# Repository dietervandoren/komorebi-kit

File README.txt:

//~~~~~~~~~~~~~~~~~~~~~~~~~~~~~~~~~~~~~~~~~~~~~~~~~~~~~~~~~~~~~~~~~~~~~~~~~~~~~
//
// KOMOREBI KIT, 2021 
//
// Created by Matteo Marangoni & Dieter Vandoren 
// Programming by Riccardo Marogna
// PCB design by Daan Johan 
//
// Info & documentation: https://instrumentinventors.org/editions/iii-sensory-kit-komorebi-instructions/ 
// GitHub: https://github.com/dietervandoren/komorebi-kit 
//
// KOMOREBI KIT is licensed under a Creative Commons Attribution-NonCommercial-ShareAlike 4.0 International License, 
// which is detailed in License.txt 
//
// KOMOREBI KIT includes the Mozzi sound synthesis library under a Creative Commons Attribution-NonCommercial-ShareAlike 4.0 International License.
// Mozzi is created by Tim Barrass, webpage: https://sensorium.github.com/Mozzi/ 
// 
//~~~~~~~~~~~~~~~~~~~~~~~~~~~~~~~~~~~~~~~~~~~~~~~~~~~~~~~~~~~~~~~~~~~~~~~~~~~~~

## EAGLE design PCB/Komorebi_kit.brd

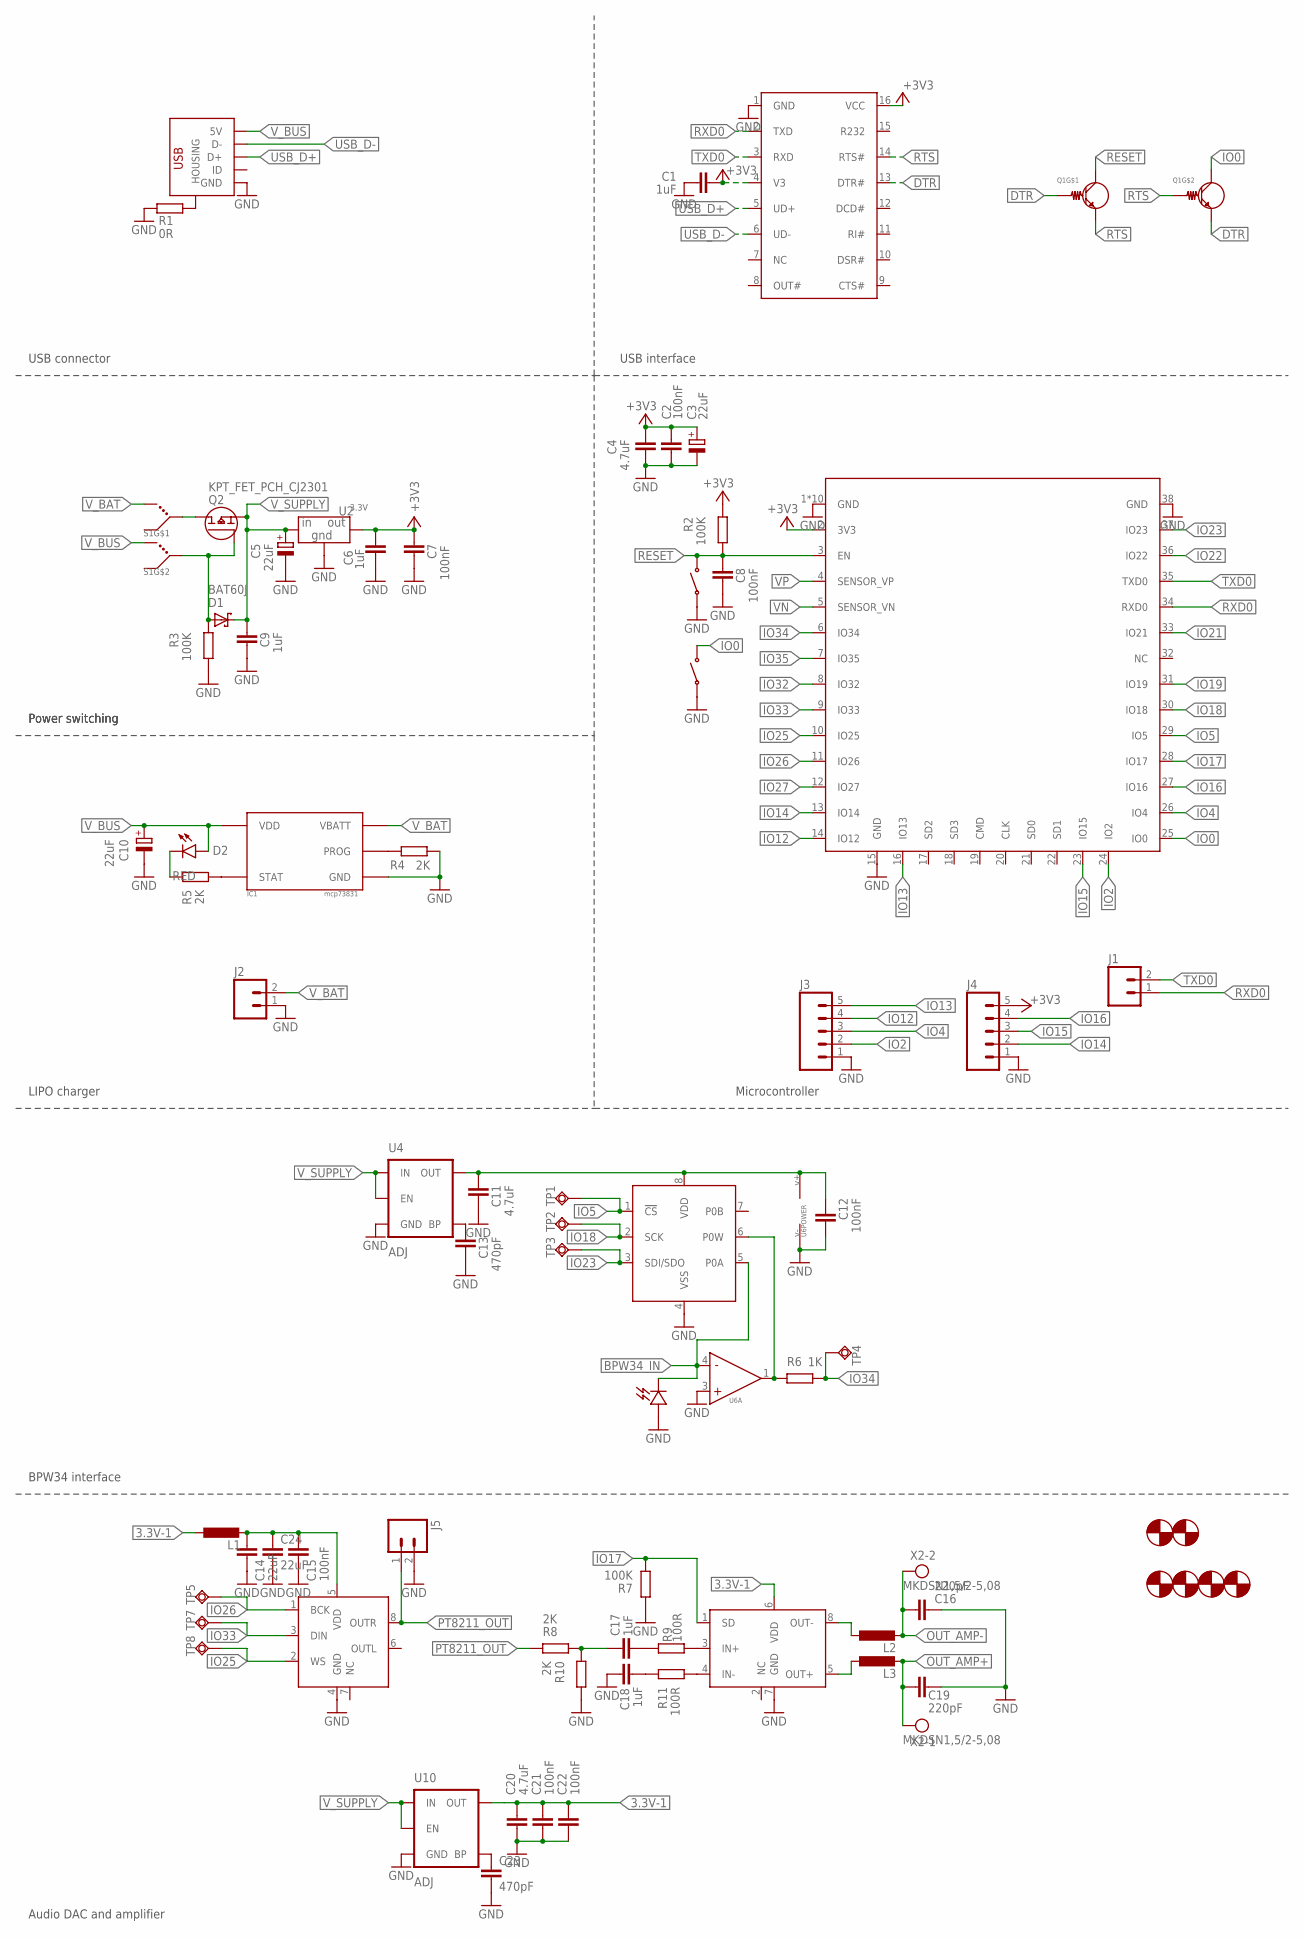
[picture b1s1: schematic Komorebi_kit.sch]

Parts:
C1, C6, C9, C17, C18: 1uF; C0603
C2, C7, C8, C12, C15, C21, C22: 100nF; C0603
C3, C5, C10: 22uF; PANASONIC_B
C4, C11, C20: 4.7uF; C0603
C13, C23: 470pF; C0603
C14, C24: 22uF; C0805
C16, C19: 220pF; C0603
D1: BAT60J; SOD323_ST
D2: RED; LED-1206
D3: KPT_SENSORS_BPW34; BPW34
H1, H2: KPT_HOLE3.0; 3.0MOUNTHOLE
H3, H4, H5, H6: KPT_HOLE4.1; 4.1MOUNTHOLE
IC1: KPT_CHARGER_MCP73831; SOT23-5
J1, J2, J5: M02PTH; 1X02
J3, J4: M05PTH; 1X05
L1, L2, L3: L-EUL2012C; L2012C
Q1: KPT_UMH3N; SOT363
Q2: KPT_FET_PCH_CJ2301; SOT23
R1: 0R; R0603
R2, R3, R7: 100K; R0603
R4, R5, R8, R10: 2K; R0603
R6: 1K; R0603
R9, R11: 100R; R0603
S1: KPT_SWITCH_JS202011AQN; C&K_JS202011AQN
S2, S3: TACT_SWITCH_C318884; SWITCH_TACTILE_C318884
TP1, TP2, TP3, TP4, TP5, TP7, TP8: TPSQB1,27; B1,27
U1: KPT_CH340C; SOIC16
U2: 3.3V; SOT-89-3L
U3: KPT_ESP32; WROOM_ESP32
U4, U10: ADJ; SOT23-5
U5: KPT_DIGIPOT_MCP41X1SOIC8; SOIC-8
U6: KPT_OPAMP_MCP6001; SOT23-5
U7: KPT_DAC_PT8211; SOIC-8
U8: KPT_AMP-D_PAM8302SOIC8; SOIC-8
X1: USB_MICROB_C10418
X2: MKDSN1,5/2-5,08

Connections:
3.3V-1: C20.1, C21.1, C22.1, L1.1, U8.6 (VDD), U10.5 (OUT)
+3V3: C1.2, C2.1, C3.+, C4.2, C6.1, C7.1, J4.5, R2.2, U1.4 (V3), U1.16 (VCC), U2.P$3 (OUT), U3.2 (3V3)
BPW34_IN: D3.CATHODE, U5.5 (P0A), U6.4 (-)
DTR: Q1.2 (BASE), Q1.4 (EMITTER), U1.13 (DTR#)
GND: C1.1, C2.2, C3.-, C4.1, C5.-, C6.2, C7.2, C8.2, C9.2, C10.-, C11.2, C12.2, C13.2, C14.2, C15.2, C16.1, C18.1, C19.1, C20.2, C21.2, C22.2, C23.2, C24.2, D3.ANODE, IC1.2 (GND), J2.1, J3.1, J4.1, J5.2, R1.1, R3.1, R4.2, R7.1, R10.1, S2.A, S2.B, S3.A, S3.B, U1.1 (GND), U2.P$1 (GND), U3.1 (GND), U3.15 (GND), U3.38 (GND), U3.BP1 (GND), U3.BP2 (GND), U3.BP3 (GND), U3.BP4 (GND), U3.BP5 (GND), U3.BP6 (GND), U3.BP7 (GND), U3.BP8 (GND), U3.BP9 (GND), U4.2 (GND), U5.4 (VSS), U6.2 (V-), U6.3 (+), U7.4 (GND), U8.7 (GND), U10.2 (GND), X1.P$1 (GND)
IN_AMP1: C17.1, R8.2, R10.2
IO0: Q1.3 (COLLECTOR), S3.C, S3.D, U3.25 (IO0)
IO2: J3.2, U3.24 (IO2)
IO4: J3.3, U3.26 (IO4)
IO5: TP1.TP, U3.29 (IO5), U5.1 (!CS!)
IO12: J3.4, U3.14 (IO12)
IO13: J3.5, U3.16 (IO13)
IO14: J4.2, U3.13 (IO14)
IO15: J4.3, U3.23 (IO15)
IO16: J4.4, U3.27 (IO16)
IO17: R7.2, U3.28 (IO17), U8.1 (SD)
IO18: TP2.TP, U3.30 (IO18), U5.2 (SCK)
IO19: U3.31 (IO19)
IO21: U3.33 (IO21)
IO22: U3.36 (IO22)
IO23: TP3.TP, U3.37 (IO23), U5.3 (SDI/SDO)
IO25: TP8.TP, U3.10 (IO25), U7.2 (WS)
IO26: TP5.TP, U3.11 (IO26), U7.1 (BCK)
IO27: U3.12 (IO27)
IO32: U3.8 (IO32)
IO33: TP7.TP, U3.9 (IO33), U7.3 (DIN)
IO34: R6.1, TP4.TP, U3.6 (IO34)
IO35: U3.7 (IO35)
unnamed: C14.1, C15.1, C24.1, L1.2, U7.5 (VDD)
unnamed: C11.1, C12.1, U4.5 (OUT), U5.8 (VDD), U6.5 (V+)
unnamed: R1.2, X1.P$6 (HOUSING), X1.P$7 (HOUSING), X1.P$8 (HOUSING), X1.P$9 (HOUSING)
unnamed: C17.2, R9.1
unnamed: C18.2, R11.1
unnamed: R9.2, U8.3 (IN+)
unnamed: IC1.5 (PROG), R4.1
unnamed: R11.2, U8.4 (IN-)
unnamed: C23.1, U10.4 (BP)
unnamed: L2.1, U8.8 (OUT-)
unnamed: L3.1, U8.5 (OUT+)
unnamed: D1.A, Q2.1 (G), R3.2, S1.P$5 (COM)
unnamed: Q2.3 (D), S1.P$2 (COM)
unnamed: D2.C, R5.1
unnamed: C13.1, U4.4 (BP)
unnamed: IC1.1 (STAT), R5.2
unnamed: R6.2, U5.6 (P0W), U6.1 (OUT)
OUT_AMP+: C19.2, L3.2, X2.1
OUT_AMP-: C16.2, L2.2, X2.2
PT8211_OUT: J5.1, R8.1, U7.8 (OUTR)
RESET: C8.1, Q1.6 (COLLECTOR), R2.1, S2.C, S2.D, U3.3 (EN)
RTS: Q1.1 (EMITTER), Q1.5 (BASE), U1.14 (RTS#)
RXD0: J1.1, U1.2 (TXD), U3.34 (RXD0)
TXD0: J1.2, U1.3 (RXD), U3.35 (TXD0)
USB_D+: U1.5 (UD+), X1.P$3 (D+)
USB_D-: U1.6 (UD-), X1.P$4 (D-)
VN: U3.5 (SENSOR_VN)
VP: U3.4 (SENSOR_VP)
V_BAT: IC1.3 (VBATT), J2.2, S1.P$3 (SW_ACTION)
V_BUS: C10.+, D2.A, IC1.4 (VDD), S1.P$6 (SW_ACTION), X1.P$5 (5V)
V_SUPPLY: C5.+, C9.1, D1.C, Q2.2 (S), U2.P$2 (IN), U2.P$4 (IN), U4.1 (IN), U4.3 (EN), U10.1 (IN), U10.3 (EN)

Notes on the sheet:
USB connector
USB interface
Power switching
LIPO charger
Microcontroller
BPW34 interface
Audio DAC and amplifier

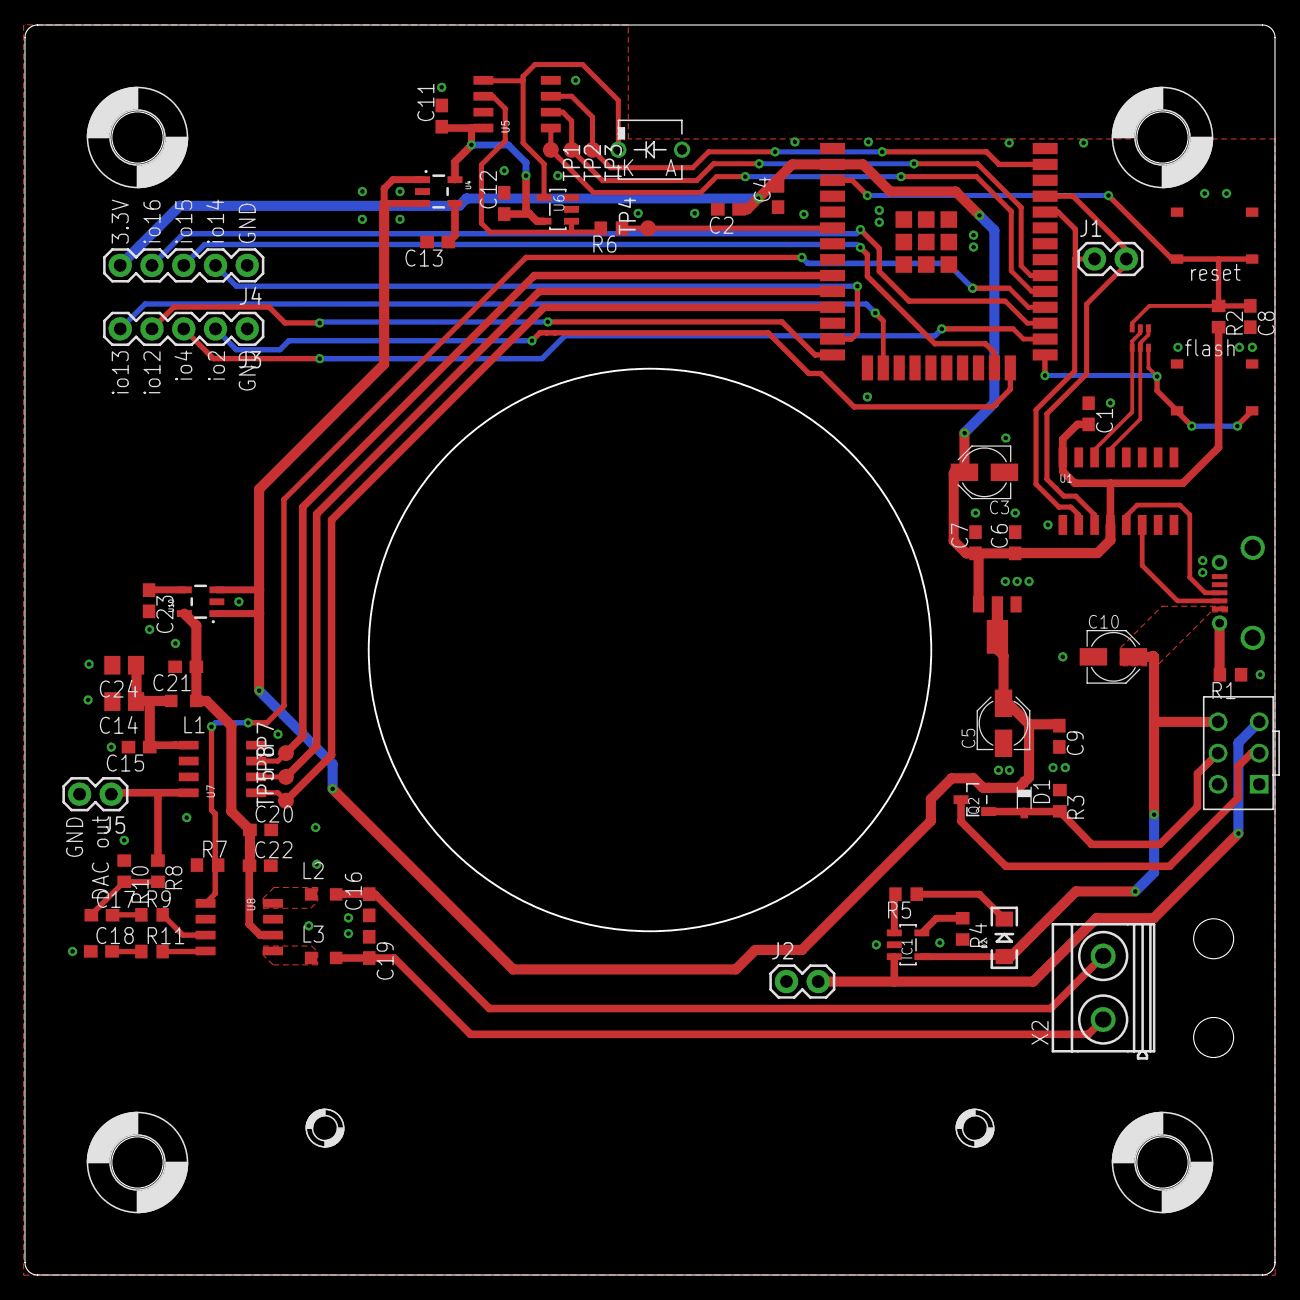
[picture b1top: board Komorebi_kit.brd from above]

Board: 2 copper layers, 99.8 x 99.8 mm, 76 parts (0 on the bottom side), 51 nets.

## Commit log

2021-05-18 initial
2021-05-18 Credit Daan
2021-06-04 PCB files added

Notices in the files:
parts and their libraries:
SparkFun-PowerIC: Licensing: Creative Commons ShareAlike 4.0 International - https://creativecommons.org/licenses/by-sa/4.0
